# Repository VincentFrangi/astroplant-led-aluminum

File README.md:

# Astroplant Led Aluminum

## About This Project

_It is recommended to use aluminum PCB for heat consideration_

[Interactive BOM](https://htmlpreview.github.io/?https://github.com/VincentFrangi/astroplant-led-aluminum/blob/master/ibom.html)

## Renderings

### Top

### Bottom

## BOM

|Count|Component|Details|Datasheet|
|-|-|-|-|
|3x|C1 / C3 / C4|CAP CER 1UF 25V X7R 0805|[Link](https://product.tdk.com/info/en/catalog/datasheets/mlcc_commercial_general_en.pdf)|
|3x|C2 / C5 / C6|CAP CER 2.7UF 25V X5R 1206||
|3x|D1 / D10 / D11|DIODE SCHOTTKY 2A 100V SMA||
|4x|D12 / D13 / D14 / D15|LED OSLON SSL120 BLUE 455NM SMD||
|4x|D16 / D17 / D18 / D19|LED OSLON SSL120 RED 727NM SMD||
|8x|D2 / D3 / D4 / D5 / D6 / D7 / D8 / D9|LED OSLON SSL120 RED 657NM SMD||
|3x|L1 / L2 / L3|FIXED IND 47UH 2.7A 100 MOHM SMD||
|1x|J2|CONN HEADER XH SMD 4POS 2.5MM||
|3x|R1 / R3 / R5|RES SMD 3.3K OHM 0.1% 1/8W 0805||
|3x|R2 / R4 / R6|RES SMD 43K OHM 0.1% 1/8W 0805||
|3x|R7 / R8 / R9|RES 0 OHM JUMPER 3/4W 2010||
|3x|RV1 / RV2 / RV3|TRIMMER 5K OHM 0.25W SMD||
|1x|U2|IC LED DRIVER RGLTR DIM 1A 8SO|[Link](http://www.ti.com/lit/ds/symlink/lm3414.pdf)|
|2x|U1 / U3|IC LED DRIVER RGLTR DIM 1A 8SO|[Link](http://www.ti.com/lit/ds/symlink/lm3414.pdf)|
|1x|J1|wago 2060 402||
---

This project is managed and available on

You can view it [here](https://aisler.net/p/KQLPCMKY). Start your own Powerful Prototype on [here](https://aisler.net).

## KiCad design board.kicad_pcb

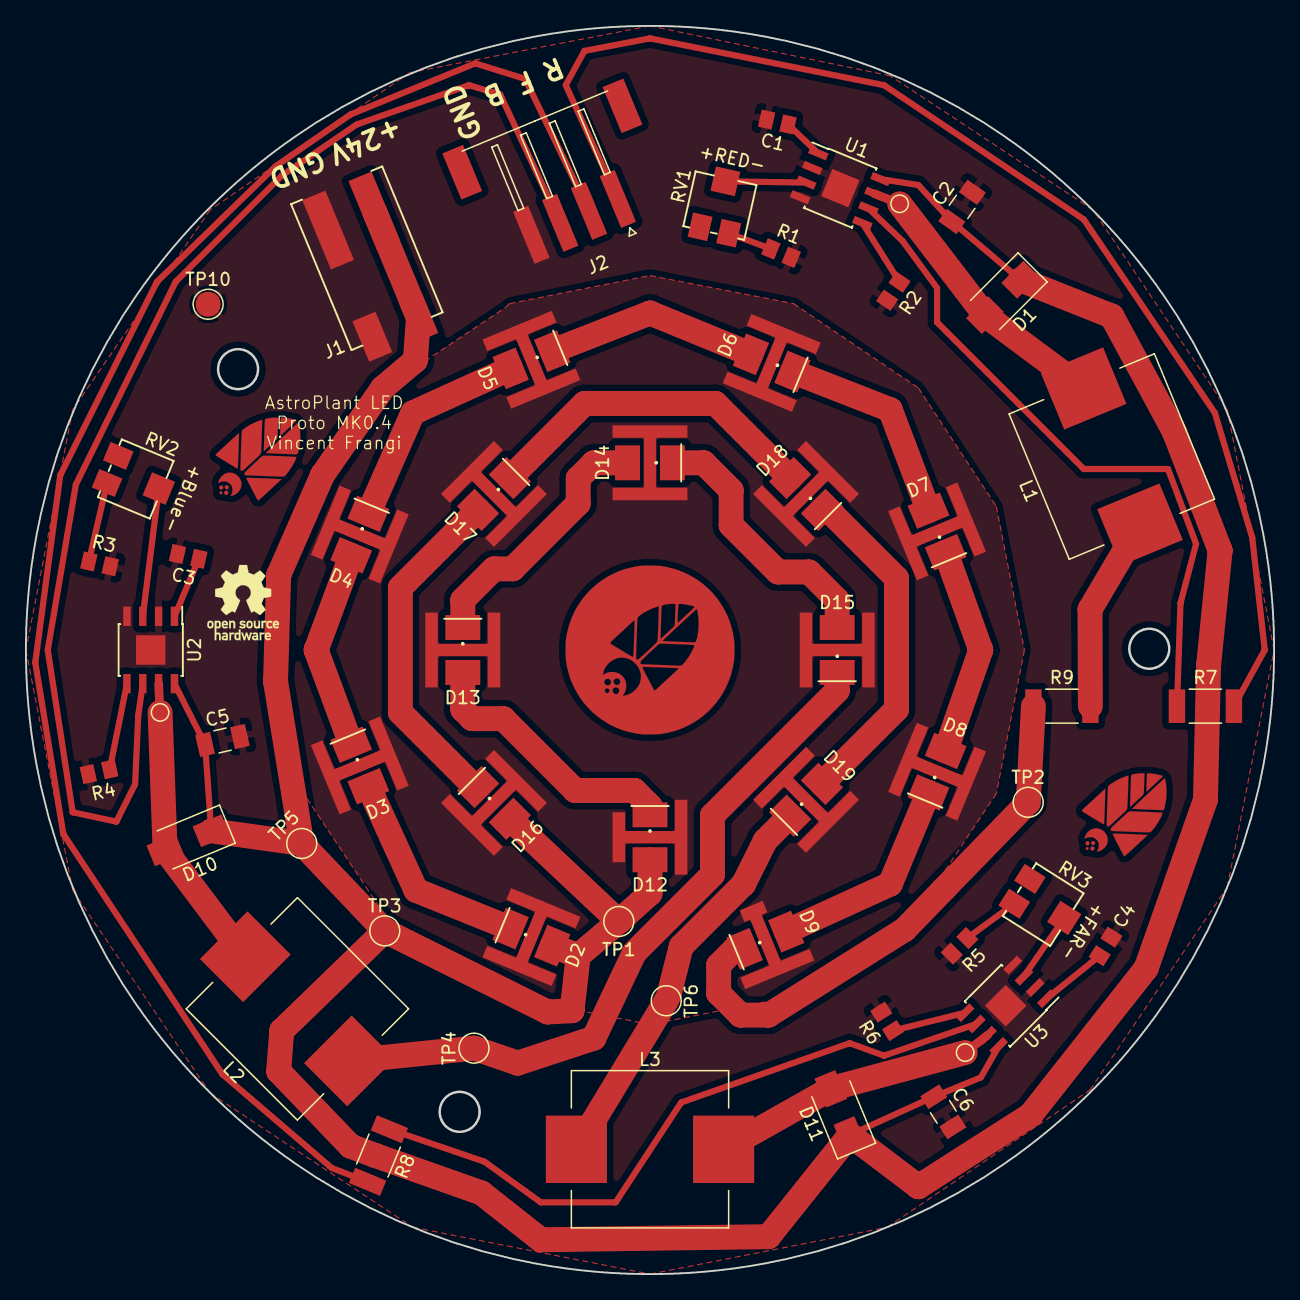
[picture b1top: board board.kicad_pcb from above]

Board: 2 copper layers, 99.9 x 99.9 mm, 55 parts (0 on the bottom side), 40 nets.

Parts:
C1, C3, C4: 1u; C_0805_2012Metric
C2, C5, C6: 2.7u; C_1206_3216Metric
D1, D10, D11: D_Schottky; D_SMA
D2, D3, D4, D5, D6, D7, D8, D9: LED_Red; SSL120
D12, D13, D14, D15: LED_Blue; SSL120
D16, D17, D18, D19: LED_Far; SSL120
J1: Conn_01x02_Wago; wago_2060_402
J2: JST-XH_LED; JST_XH_LED_POWER
L1, L2, L3: 47u; L_Wuerth_WE-PD-Typ-LS_Handsoldering
R1, R3, R5: 3.3k; R_0805_2012Metric
R2, R4, R6: 43k; R_0805_2012Metric
R7, R8, R9: 0; R_2010_5025Metric
RV1, RV2, RV3: 5k; ST4ETA502
TP1, TP3: Test_Point; TestPoint_Pad_D2.0mm
TP2: Red; TestPoint_Pad_D2.0mm
TP4: Blue; TestPoint_Pad_D2.0mm
TP5: +24V; TestPoint_Pad_D2.0mm
TP6: Far; TestPoint_Pad_D2.0mm
TP7, TP8, TP9: Test_Point; TestPoint_Pad_D1.0mm
TP10: GND; TestPoint_Pad_D2.0mm
U1, U2, U3: LM3414; SOIC-8-1EP_3.9x4.9mm_P1.27mm_EP2.35x2.35mm

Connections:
+24V: C2.1, C5.1, C6.1, D1.1, D2.2, D10.1, D11.1, D12.2, D16.2, J1.2, TP1.1, TP3.1, TP5.1, U1.8, U2.8, U3.8
DIM_BLUE: J2.3, U2.6
DIM_FAR: R8.1, U3.6
DIM_RED: R7.1, U1.6
GND: C1.2, C2.2, C3.2, C4.2, C5.2, C6.2, J1.1, J2.4, R1.2, R2.2, R3.2, R4.2, R5.2, R6.2, TP10.1, U1.2, U1.4, U1.9, U2.2, U2.4, U2.9, U3.2, U3.4, U3.9
unnamed: C1.1, U1.1
unnamed: C3.1, U2.1
unnamed: C4.1, U3.1
unnamed: D1.2, L1.2, TP7.1, U1.7
unnamed: D2.1, D3.2
unnamed: D3.1, D4.2
unnamed: D4.1, D5.2
unnamed: D5.1, D6.2
unnamed: D6.1, D7.2
unnamed: D7.1, D8.2
unnamed: D8.1, D9.2
unnamed: D9.1, R9.1, TP2.1
unnamed: D10.2, L2.2, TP8.1, U2.7
unnamed: D11.2, L3.2, TP9.1, U3.7
unnamed: D12.1, D13.2
unnamed: D13.1, D14.2
unnamed: D14.1, D15.2
unnamed: D15.1, L2.1, TP4.1
unnamed: D16.1, D17.2
unnamed: D17.1, D18.2
unnamed: D18.1, D19.2
unnamed: D19.1, L3.1, TP6.1
unnamed: J2.1, R7.2
unnamed: J2.2, R8.2
unnamed: L1.1, R9.2
unnamed: R1.1, RV1.1
unnamed: R2.1, U1.5
unnamed: R3.1, RV2.1
unnamed: R4.1, U2.5
unnamed: R5.1, RV3.1
unnamed: R6.1, U3.5
unnamed: RV1.2, U1.3
unnamed: RV2.2, U2.3
unnamed: RV3.2, U3.3
Therm_pad: D2.3, D3.3, D4.3, D5.3, D6.3, D7.3, D8.3, D9.3, D12.3, D13.3, D14.3, D15.3, D16.3, D17.3, D18.3, D19.3

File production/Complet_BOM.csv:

Component,Description,Part,References,Value,Footprint,Quantity Per PCB,Datasheet,Digikey PN,MPN
1,Unpolarized capacitor,C_Small,C1 C3 C4,1u,C_0805_2012Metric,3,https://product.tdk.com/info/en/catalog/datasheets/mlcc_comm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,445-1354-1-ND,C2012X7R1E105K125AB
2,Unpolarized capacitor,C_Small,C2 C5 C6,2.7u,C_1206_3216Metric,3,https://search.kemet.com/component-edge/download/datasheet/C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,399-3139-1-ND,C1206C275K3PACTU
3,Schottky diode,D_Schottky,D1 D10 D11,D_Schottky,D_SMA,3,https://www.fairchildsemi.com/datasheets/SS/SSA210.pdf,SSA210CT-ND,SSA210
4,LED with pad,LED_PAD,D12 D13 D14 D15,LED_Blue,SSL120,4,https://dammedia.osram.info/media/resource/hires/osram-dam-4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,475-3273-1-ND,GD CSSPM1.14-UOVJ-W4-1
5,LED with pad,LED_PAD,D16 D17 D18 D19,LED_Far,SSL120,4,https://dammedia.osram.info/media/resource/hires/osram-dam-4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,475-3276-1-ND,GF CSSPM1.24-4S2T-1
6,LED with pad,LED_PAD,D2 D3 D4 D5 D6 D7 D8 D9,LED_Red,SSL120,8,https://dammedia.osram.info/media/resource/hires/osram-dam-4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,475-3279-1-ND,GH CSSPM1.24-4T2U-1
7,"Generic connector, single row, 01x02, script generated (kicad-library-utils/schlib/autogen/connector/)",Conn_01x02_Female,J1,Conn_01x02_Wago,wago_2060_402,1,https://www.wago.com/infomaterial/pdf/51300133.pdf,,2060-402/998-404
8,CONN HEADER XH TOP 4POS 2.5MM,JST-XH_LED_GND,J2,JST-XH_LED,JST_XH_LED_POWER,1,http://www.jst-mfg.com/product/pdf/eng/eXH.pdf,455-2262-1-ND,S4B-XH-SM4-TB(LF)(SN)
9,Inductor,L,L1 L2 L3,47u,L_Wuerth_WE-PD-Typ-LS_Handsoldering,3,http://katalog.we-online.de/pbs/datasheet/744770147.pdf,732-1231-1-ND,744770147
10,"Resistor, small symbol",R_Small,R7 R8 R9,0,R_2010_5025Metric,3,https://www.seielect.com/Catalog/SEI-RMCF_RMCP.pdf,RMCF2010ZT0R00CT-ND,RMCF2010ZT0R00
11,"Resistor, small symbol",R_Small,R1 R3 R5,3.3k,R_0805_2012Metric,3,https://industrial.panasonic.com/cdbs/www-data/pdf/RDM0000/A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,P3.3KDACT-ND,ERA-6AEB332V
12,"Resistor, small symbol",R_Small,R2 R4 R6,43k,R_0805_2012Metric,3,https://industrial.panasonic.com/cdbs/www-data/pdf/RDM0000/A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,P43KDACT-ND,ERA-6AEB433V
13,Potentiometer,R_POT,RV1 RV2 RV3,5k,ST4ETA502,3,https://www.nidec-copal-electronics.com/e/catalog/trimmer/st-4.pdf,ST4ETA502CT-ND,ST4ETA502
14,"LED Driver IC 1 Output DC DC Regulator Step-Down (Buck) Analog, PWM Dimming 1A 8-SO PowerPad",LM3414,U1 U2 U3,LM3414,SOIC-8-1EP_3.9x4.9mm_P1.27mm_EP2.35x2.35mm,3,http://www.ti.com/lit/ds/symlink/lm3414.pdf,296-41304-1-ND,LM3414MRX/NOPB





Component Groups:,14
Component Count:,45
Fitted Components:,45
Number of PCBs:,1
Total components:,45
Schematic Version:,0.3
Schematic Date:,2018-07-02
BoM Date:,mar 03 jui 2018 19:47:01 UTC
Schematic Source:,/home/vincent/Documents/AstroPlant_VFR/Project/Electronics/PCB/Peripheral/LEDs/kicad/Astroplant_LED_Alu/Astroplant_LED.sch
KiCad Version:,Eeschema (5.0.0-rc3-dev)

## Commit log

2018-10-08 Syncing AISLER project with GitHub repository
2018-10-08 Add Schematics and production files
2018-11-08 Add 3d model
2018-11-15 Add interactive BOM
2018-11-27 Add position files
